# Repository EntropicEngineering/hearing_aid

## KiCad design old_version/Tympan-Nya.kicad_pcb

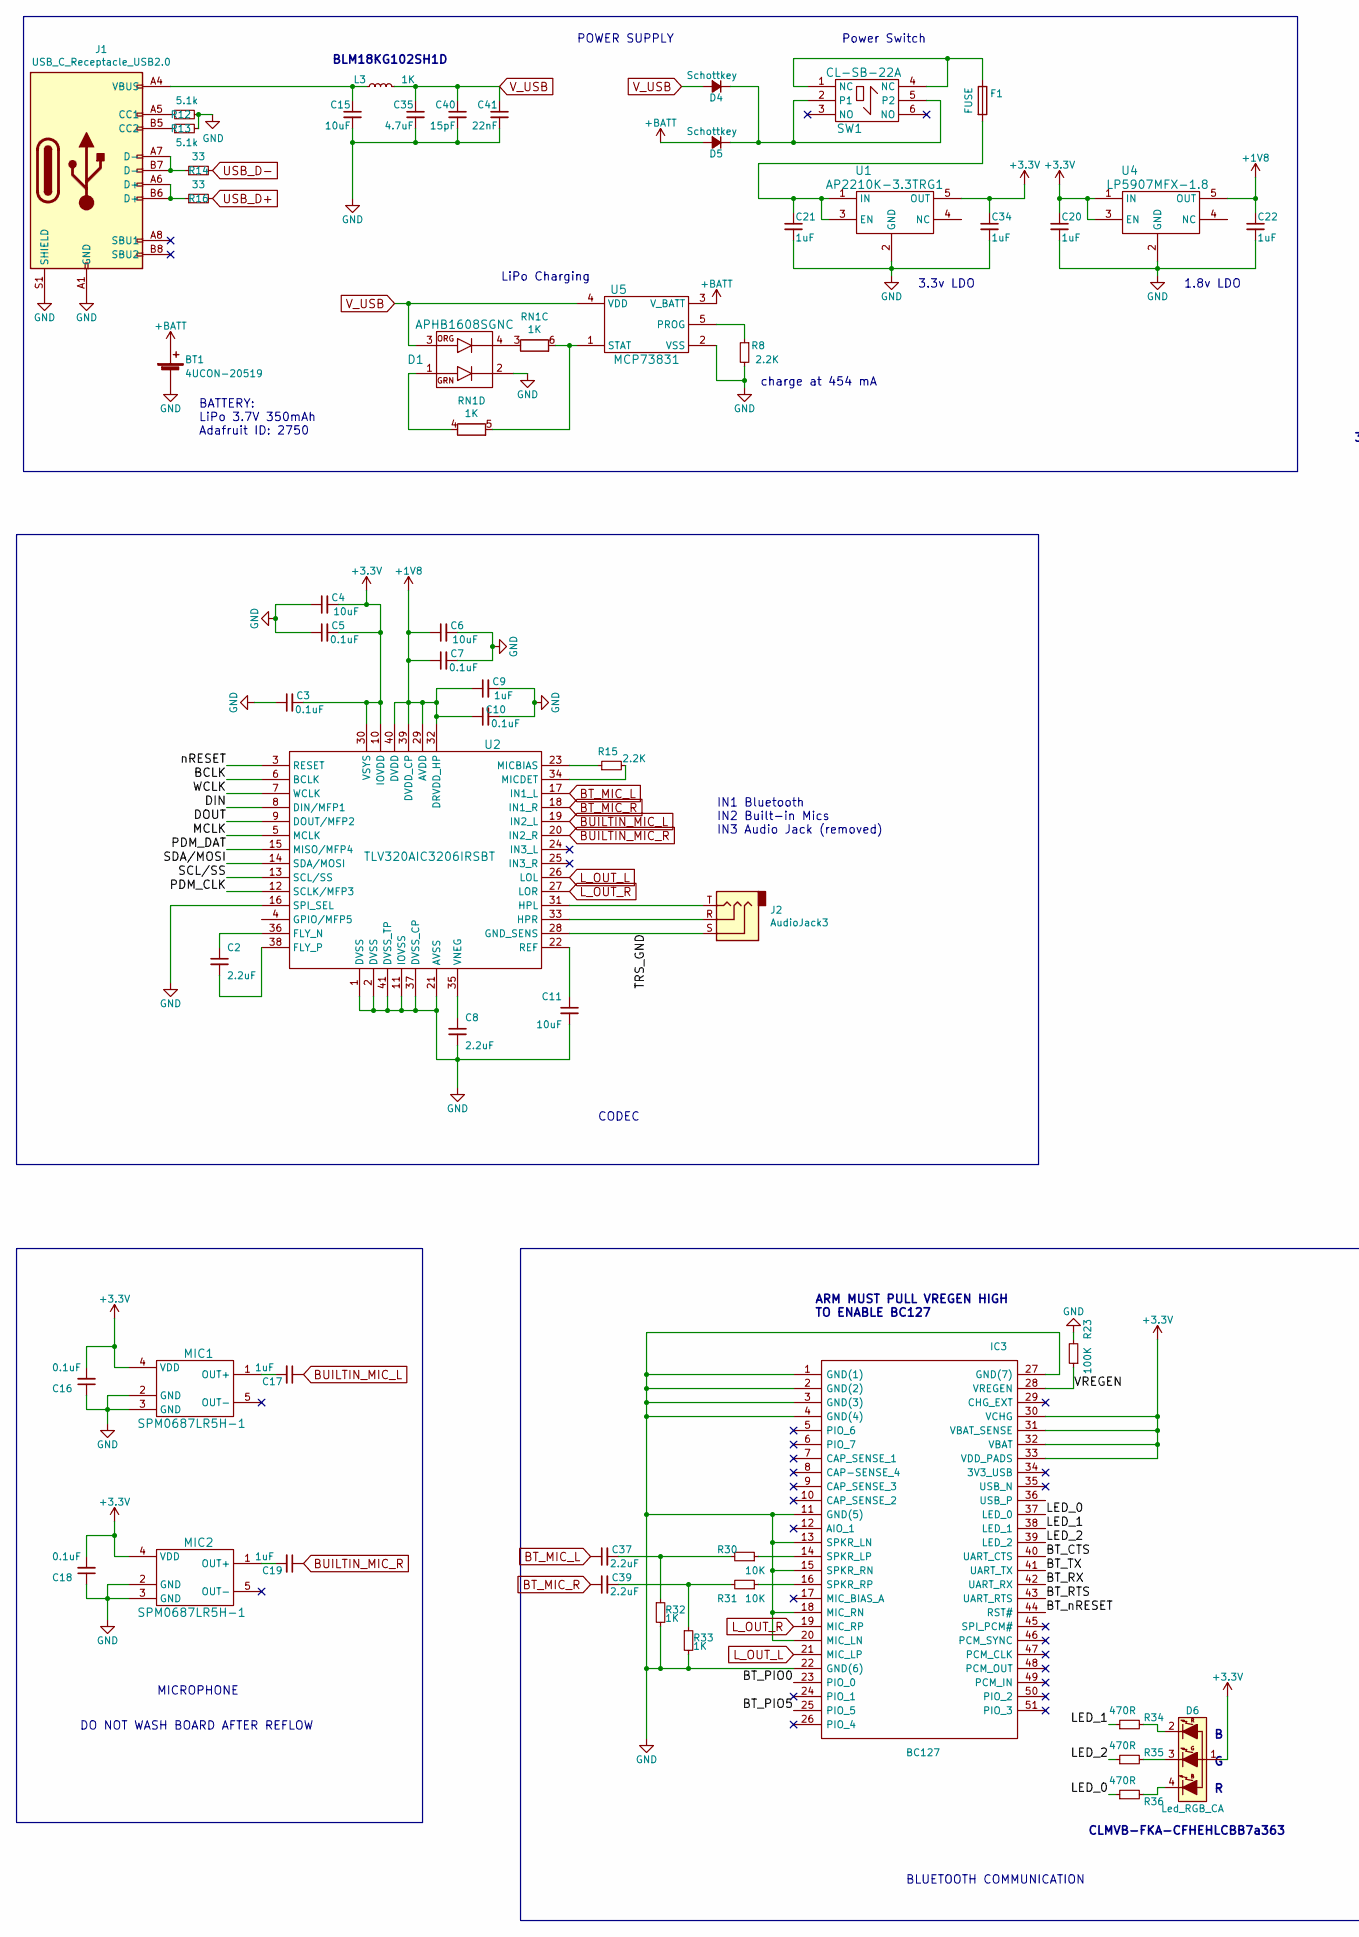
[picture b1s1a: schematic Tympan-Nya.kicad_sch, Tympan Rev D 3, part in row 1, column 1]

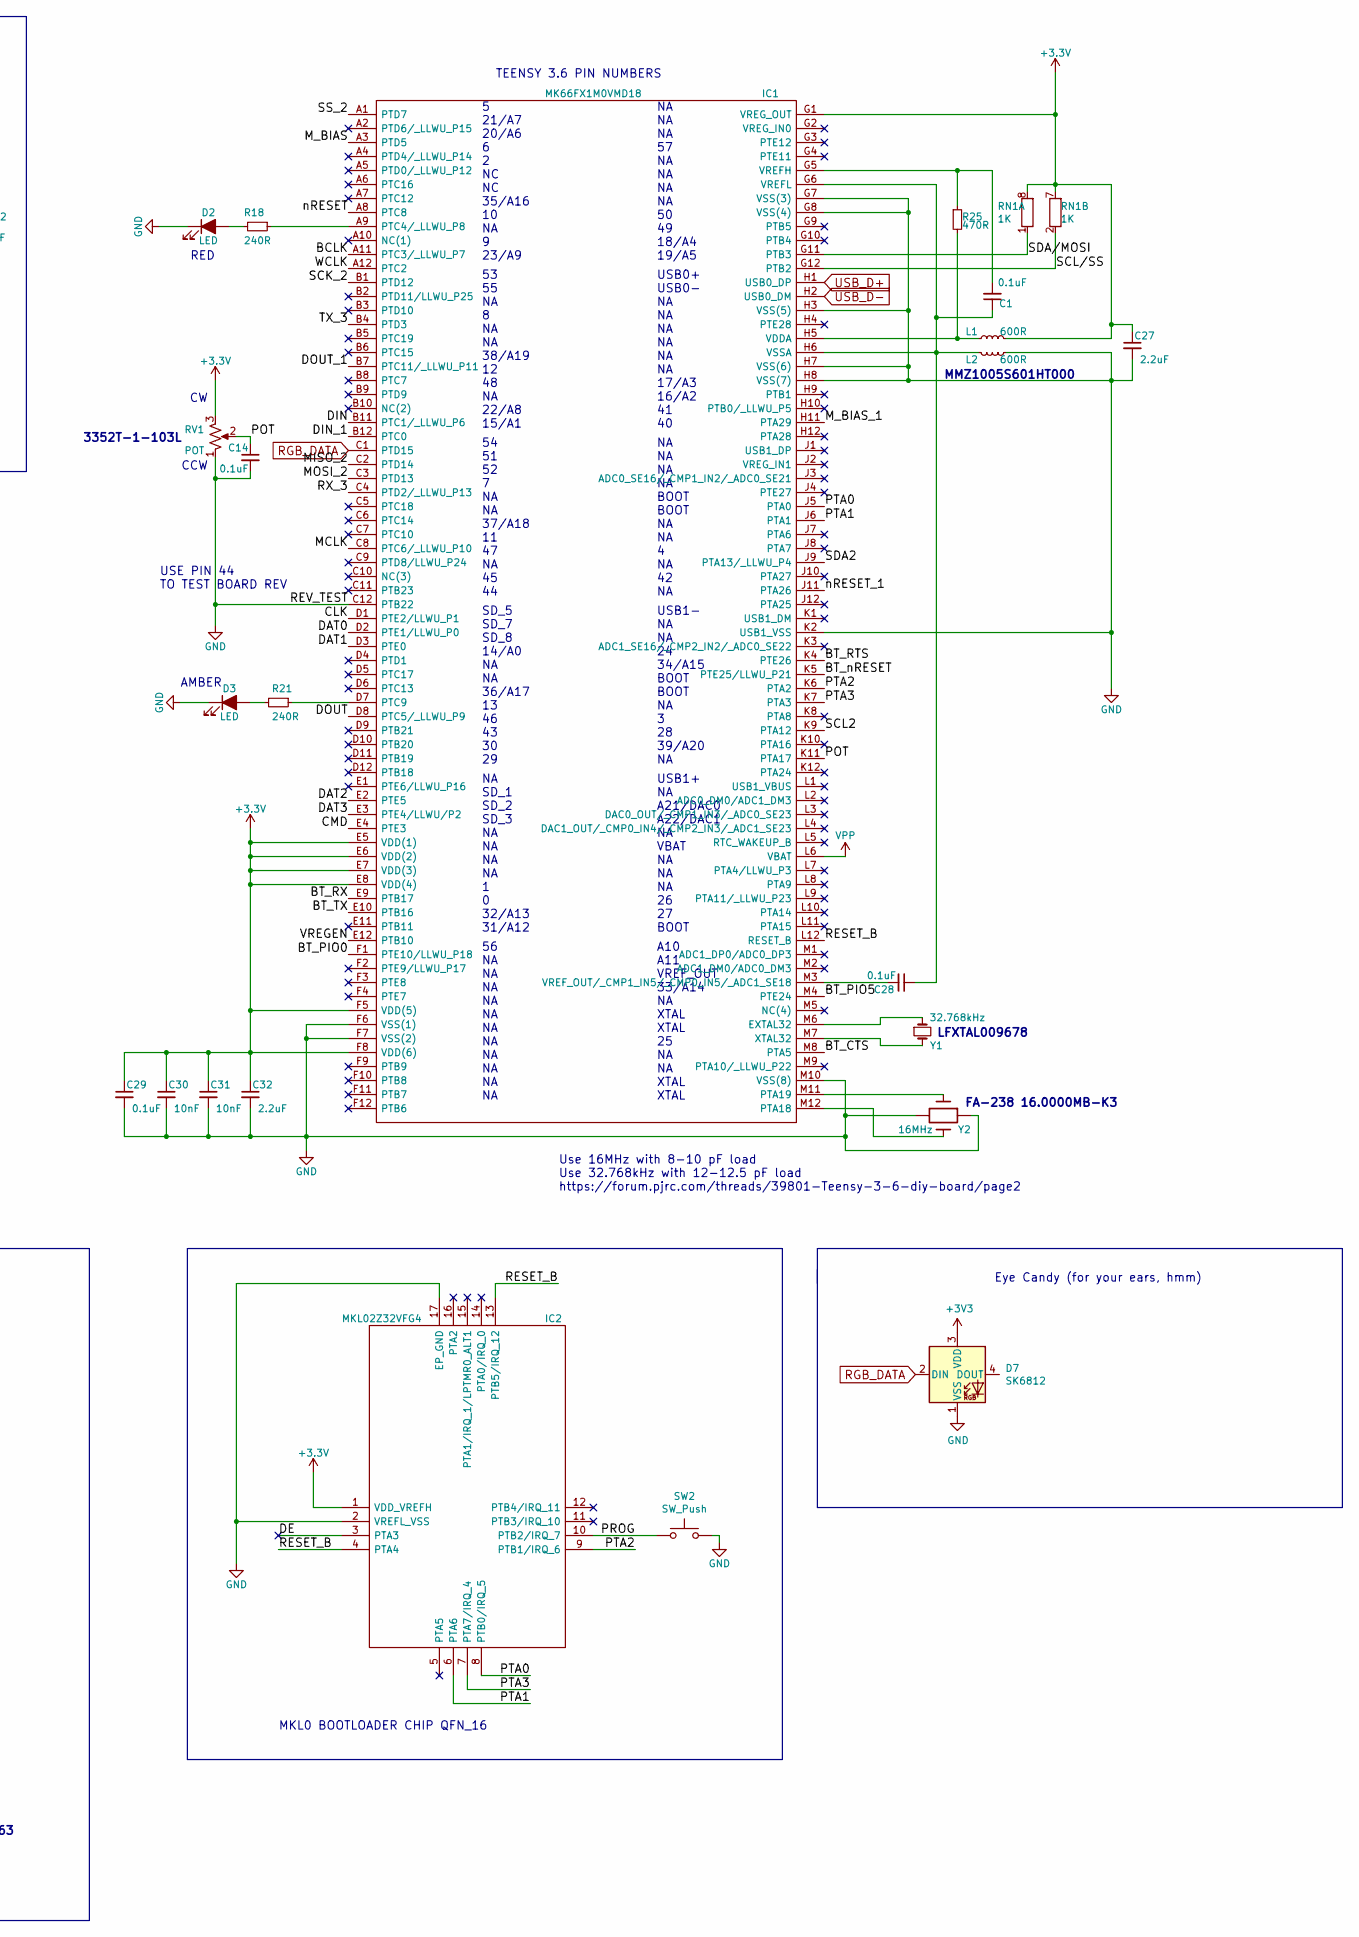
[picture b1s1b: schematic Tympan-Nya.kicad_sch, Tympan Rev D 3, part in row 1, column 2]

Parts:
BT1: 4UCON-20519; 4UCON-0217-20519
C1, C3, C5, C7, C10, C14, C16, C18, C28, C29: 0.1uF; C_0402_1005Metric
C2, C8, C27, C32, C37, C39: 2.2uF; C_0402_1005Metric
C4, C6, C11, C15: 10uF; C_0402_1005Metric
C9, C17, C19, C20, C21, C22, C34: 1uF; C_0402_1005Metric
C30, C31: 10nF; C_0402_1005Metric
C35: 4.7uF; C_0402_1005Metric
C40: 15pF; C_0402_1005Metric
C41: 22nF; C_0402_1005Metric
D1: APHB1608SGNC; ABHB1608S
D2, D3: LED; LED_0805_2012Metric
D4, D5: Schottkey; ACDBA340-HF
D6: Led_RGB_CA; CLMVB-FKA-CFHEHLCBB7a363
D7: SK6812; LED_SK6812_PLCC4_5.0x5.0mm_P3.2mm
F1: FUSE; Fuse_1206_3216Metric
IC1: MK66FX1M0VMD18; BGA-144_13.0x13.0mm_Layout12x12_P1.0mm; Manufacturer_Part_Number MK66FX1M0VMD18
IC2: MKL02Z32VFG4; QFN-16-1EP_3x3mm_P0.5mm_EP1.7x1.7mm; Manufacturer_Part_Number MKL02Z32VFG4
IC3: BC127; Manufacturer_Part_Number bc127
J1: USB_C_Receptacle_USB2.0; USB_C_Receptacle_HRO_TYPE-C-31-M-12
J2: AudioJack3; Jack_3.5mm_CUI_SJ-3523-SMT_Horizontal; DigiKey SJ-2523-SMT-TR
L1, L2: 600R; L_0402_1005Metric
L3: 1K; L_0603_1608Metric
MIC1, MIC2: SPM0687LR5H-1
R8, R15: 2.2K; R_0402_1005Metric
R12, R13: 5.1k; R_0402_1005Metric
R14, R16: 33; R_0402_1005Metric
R18, R21: 240R; R_0402_1005Metric
R23: 100K; R_0402_1005Metric
R25, R34, R35, R36: 470R; R_0402_1005Metric
R30, R31: 10K; R_0402_1005Metric
R32, R33: 1K; R_0402_1005Metric
RN1: 1K; R_Array_Convex_4x0603
RV1: POT; PinHeader_1x03_P2.54mm_Vertical
SW1: CL-SB-22A
SW2: SW_Push; SW_SPST_TL3342
U1: AP2210K-3.3TRG1; SOT-23-5
U2: TLV320AIC3206IRSBT; UQFN-40-1EP_5x5mm_P0.4mm_EP3.8x3.8mm
U4: LP5907MFX-1.8; SOT-23-5
U5: MCP73831; SOT-23-5
Y1: 32.768kHz; LFXTAL009678
Y2: 16MHz; FA_238_16.0000MB_K3

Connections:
+1V8: C6.1, C7.1, C9.1, C10.1, C22.1, U2.29 (AVDD), U2.32 (DRVDD_HP), U2.39 (DVDD_CP), U2.40 (DVDD), U4.5 (OUT)
+BATT: BT1.1 (+), D5.2 (A), U5.3 (V_BATT)
/BCLK: IC1.A11 (PTC3/_LLWU_P7), U2.6 (BCLK)
/BT_CTS: IC1.M8 (PTA5), IC3.40 (UART_CTS)
/BT_PIO0: IC1.F1 (PTE10/LLWU_P18), IC3.23 (PIO_0)
/BT_PIO5: IC1.M4 (PTE24), IC3.25 (PIO_5)
/BT_RTS: IC1.K4 (PTE26), IC3.43 (UART_RTS)
/BT_RX: IC1.E9 (PTB17), IC3.42 (UART_RX)
/BT_TX: IC1.E10 (PTB16), IC3.41 (UART_TX)
/BT_nRESET: IC1.K5 (PTE25/LLWU_P21), IC3.44 (RST#)
/CLK: IC1.D1 (PTE2/LLWU_P1)
/CMD: IC1.E4 (PTE3)
/DAT0: IC1.D2 (PTE1/LLWU_P0)
/DAT1: IC1.D3 (PTE0)
/DAT2: IC1.E2 (PTE5)
/DAT3: IC1.E3 (PTE4/LLWU/P2)
/DE: IC2.3 (PTA3)
/DIN: IC1.B11 (PTC1/_LLWU_P6), U2.8 (DIN/MFP1)
/DIN_1: IC1.B12 (PTC0)
/DOUT: IC1.D8 (PTC5/_LLWU_P9), U2.9 (DOUT/MFP2)
/DOUT_1: IC1.B7 (PTC11/_LLWU_P11)
/LED_0: IC3.37 (LED_0), R36.1
/LED_1: IC3.38 (LED_1), R34.1
/LED_2: IC3.39 (LED_2), R35.1
/MCLK: IC1.C8 (PTC6/_LLWU_P10), U2.5 (MCLK)
/MISO_2: IC1.C2 (PTD14)
/MOSI_2: IC1.C3 (PTD13)
/M_BIAS: IC1.A3 (PTD5)
/M_BIAS_1: IC1.H11 (PTA29)
/PDM_CLK: U2.12 (SCLK/MFP3)
/PDM_DAT: U2.15 (MISO/MFP4)
/POT: C14.1, IC1.K11 (PTA17), RV1.2
/PROG: IC2.10 (PTB2/IRQ_7), SW2.1
/PTA0: IC1.J5 (PTA0), IC2.8 (PTB0/IRQ_5)
/PTA1: IC1.J6 (PTA1), IC2.6 (PTA6)
/PTA2: IC1.K6 (PTA2), IC2.9 (PTB1/IRQ_6)
/PTA3: IC1.K7 (PTA3), IC2.7 (PTA7/IRQ_4)
/RESET_B: IC1.L12 (RESET_B), IC2.4 (PTA4), IC2.13 (PTB5/IRQ_12)
/RX_3: IC1.C4 (PTD2/_LLWU_P13)
/SCK_2: IC1.B1 (PTD12)
/SCL2: IC1.K9 (PTA12)
/SCL/SS: IC1.G12 (PTB2), RN1.2 (R2.1), U2.13 (SCL/SS)
/SDA2: IC1.J9 (PTA13/_LLWU_P4)
/SDA/MOSI: IC1.G11 (PTB3), RN1.1 (R1.1), U2.14 (SDA/MOSI)
/SS_2: IC1.A1 (PTD7)
/TRS_GND: J2.S, U2.28 (GND_SENS)
/TX_3: IC1.B4 (PTD3)
/VREGEN: IC1.E12 (PTB10), IC3.28 (VREGEN), R23.1
/WCLK: IC1.A12 (PTC2), U2.7 (WCLK)
/nRESET: IC1.A8 (PTC8), U2.3 (RESET)
/nRESET_1: IC1.J11 (PTA26)
BT_MIC_L: C37.1, U2.17 (IN1_L)
BT_MIC_R: C39.1, U2.18 (IN1_R)
BUILTIN_MIC_L: C17.1, U2.19 (IN2_L)
BUILTIN_MIC_R: C19.1, U2.20 (IN2_R)
GND: BT1.2 (-), C3.1, C4.1, C5.1, C6.2, C7.2, C8.2, C9.2, C10.2, C11.2, C14.2, C15.2, C16.1, C18.1, C20.2, C21.2, C22.2, C27.2, C29.2, C30.2, C31.2, C32.2, C34.2, C35.2, C40.2, C41.2, D1.2, D2.1 (K), D3.1 (K), D7.1 (VSS), IC1.C12 (PTB22), IC1.F6 (VSS(1)), IC1.F7 (VSS(2)), IC1.G7 (VSS(3)), IC1.G8 (VSS(4)), IC1.H3 (VSS(5)), IC1.H7 (VSS(6)), IC1.H8 (VSS(7)), IC1.K2 (USB1_VSS), IC1.M10 (VSS(8)), IC2.2 (VREFL_VSS), IC2.17 (EP_GND), IC3.1 (GND(1)), IC3.2 (GND(2)), IC3.3 (GND(3)), IC3.4 (GND(4)), IC3.11 (GND(5)), IC3.13 (SPKR_LN), IC3.15 (SPKR_RN), IC3.18 (MIC_RN), IC3.20 (MIC_LN), IC3.22 (GND(6)), IC3.27 (GND(7)), J1.A1 (GND), J1.A12 (GND), J1.B1 (GND), J1.B12 (GND), J1.S1 (SHIELD), L2.2, MIC1.2 (GND), MIC1.3 (GND), MIC2.2 (GND), MIC2.3 (GND), R8.2, R12.2, R13.2, R23.2, R32.2, R33.2, RV1.1, SW2.2, U1.2 (GND), U2.1 (DVSS), U2.2 (DVSS), U2.11 (IOVSS), U2.16 (SPI_SEL), U2.21 (AVSS), U2.37 (DVSS_CP), U2.41 (DVSS_TP), U4.2 (GND), U5.2 (VSS), Y2.2, Y2.4
L_OUT_L: IC3.21 (MIC_LP), U2.26 (LOL)
L_OUT_R: IC3.19 (MIC_RP), U2.27 (LOR)
unnamed: C1.1, C28.1, IC1.G6 (VREFL), IC1.H6 (VSSA), L2.1
unnamed: C1.2, IC1.G5 (VREFH), R25.1
unnamed: C2.1, U2.36 (FLY_N)
unnamed: C2.2, U2.38 (FLY_P)
unnamed: C8.1, U2.35 (VNEG)
unnamed: C11.1, U2.22 (REF)
unnamed: C15.1, J1.A4 (VBUS), J1.A9 (VBUS), J1.B4 (VBUS), J1.B9 (VBUS), L3.1
unnamed: C17.2, MIC1.1 (OUT+)
unnamed: C19.2, MIC2.1 (OUT+)
unnamed: C21.1, F1.2, U1.1 (IN), U1.3 (EN)
unnamed: C28.2, IC1.M3 (VREF_OUT/_CMP1_IN5/_CMP0_IN5/_ADC1_SE18)
unnamed: C37.2, R30.2, R32.1
unnamed: C39.2, R31.2, R33.1
unnamed: D1.1, RN1.4 (R4.1)
unnamed: D1.4, RN1.3 (R3.1)
unnamed: D2.2 (A), R18.2
unnamed: D3.2 (A), R21.2
unnamed: D4.1 (K), D5.1 (K), SW1.2 (P1), SW1.5 (P2)
unnamed: D6.2 (R), R34.2
unnamed: D6.3 (G), R35.2
unnamed: D6.4 (B), R36.2
unnamed: F1.1, SW1.1 (NC), SW1.4 (NC)
unnamed: IC1.A9 (PTC4/_LLWU_P8), R18.1
unnamed: IC1.D7 (PTC9), R21.1
unnamed: IC1.H5 (VDDA), L1.1, R25.2
unnamed: IC1.M6 (EXTAL32), Y1.1
unnamed: IC1.M7 (XTAL32), Y1.2
unnamed: IC1.M11 (PTA19), Y2.1
unnamed: IC1.M12 (PTA18), Y2.3
unnamed: IC3.14 (SPKR_LP), R30.1
unnamed: IC3.16 (SPKR_RP), R31.1
unnamed: J1.A5 (CC1), R12.1
unnamed: J1.A6 (D+), J1.B6 (D+), R16.1
unnamed: J1.A7 (D-), J1.B7 (D-), R14.1
unnamed: J1.B5 (CC2), R13.1
unnamed: J2.R, U2.33 (HPR)
unnamed: J2.T, U2.31 (HPL)
unnamed: R8.1, U5.5 (PROG)
unnamed: R15.1, U2.23 (MICBIAS)
unnamed: R15.2, U2.34 (MICDET)
unnamed: RN1.5 (R4.2), RN1.6 (R3.2), U5.1 (STAT)
RGB_DATA: D7.2 (DIN), IC1.C1 (PTD15)
USB_D+: IC1.H1 (USB0_DP), R16.2
USB_D-: IC1.H2 (USB0_DM), R14.2
VPP: IC1.L6 (VBAT)
V_USB: C35.1, C40.1, C41.1, D1.3, D4.2 (A), L3.2, U5.4 (VDD)

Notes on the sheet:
DO NOT WASH BOARD AFTER REFLOW
MICROPHONE
BATTERY: LiPo 3.7V 350mAh Adafruit ID: 2750
BLM18KG102SH1D
POWER SUPPLY
LiPo Charging
CODEC
IN1 Bluetooth IN2 Built-in Mics IN3 Audio Jack (removed)
ARM MUST PULL VREGEN HIGH TO ENABLE BC127
charge at 454 mA
BLUETOOTH COMMUNICATION
Power Switch
3.3v LDO
CLMVB-FKA-CFHEHLCBB7a363
B G R
1.8v LDO
3352T-1-103L
USE PIN 44 TO TEST BOARD REV
CW CCW
RED
AMBER
MKL0 BOOTLOADER CHIP QFN_16
5 21/A7 20/A6 6 2 NC NC 35/A16 10 NA 9 23/A9
53 55 NA 8 NA NA 38/A19 12 48 NA 22/A8 15/A1
54 51 52 7 NA NA 37/A18 11 47 NA 45 44
SD_5 SD_7 SD_8 14/A0 NA NA 36/A17 13 46 43 30 29
NA SD_1 SD_2 SD_3 NA NA NA NA 1 0 32/A13 31/A12
56 NA NA NA NA NA NA NA NA NA NA NA
TEENSY 3.6 PIN NUMBERS
Use 16MHz with 8-10 pF load Use 32.768kHz with 12-12.5 pF load https://forum.pjrc.com/threads/39801-Teensy-3-6-diy-board/page2
NA NA NA 57 NA NA NA NA 50 49 18/A4 19/A5
USB0+ USB0- NA NA NA NA NA NA 17/A3 16/A2 41 40
NA NA NA NA BOOT BOOT NA NA 4 NA 42 NA
USB1- NA NA 24 34/A15 BOOT BOOT NA 3 28 39/A20 NA
USB1+ NA A21/DAC0 A22/DAC1 NA VBAT NA NA NA 26 27 BOOT
A10 A11 VREF_OUT 33/A14 NA XTAL XTAL 25 NA NA XTAL XTAL
LFXTAL009678
MMZ1005S601HT000
FA-238 16.0000MB-K3
Eye Candy (for your ears, hmm)

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
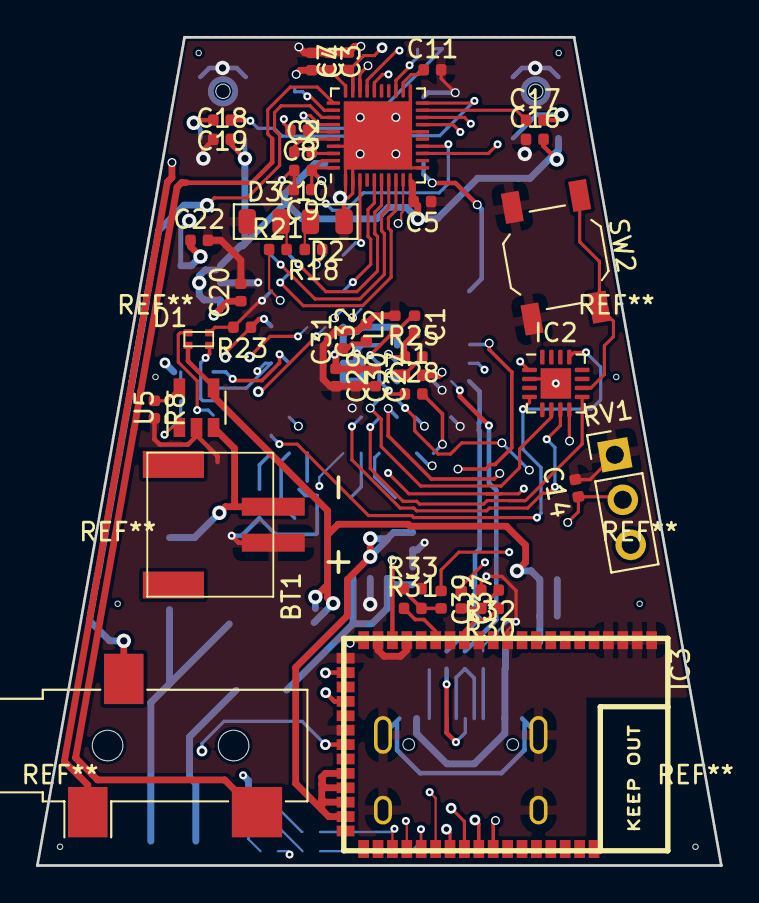
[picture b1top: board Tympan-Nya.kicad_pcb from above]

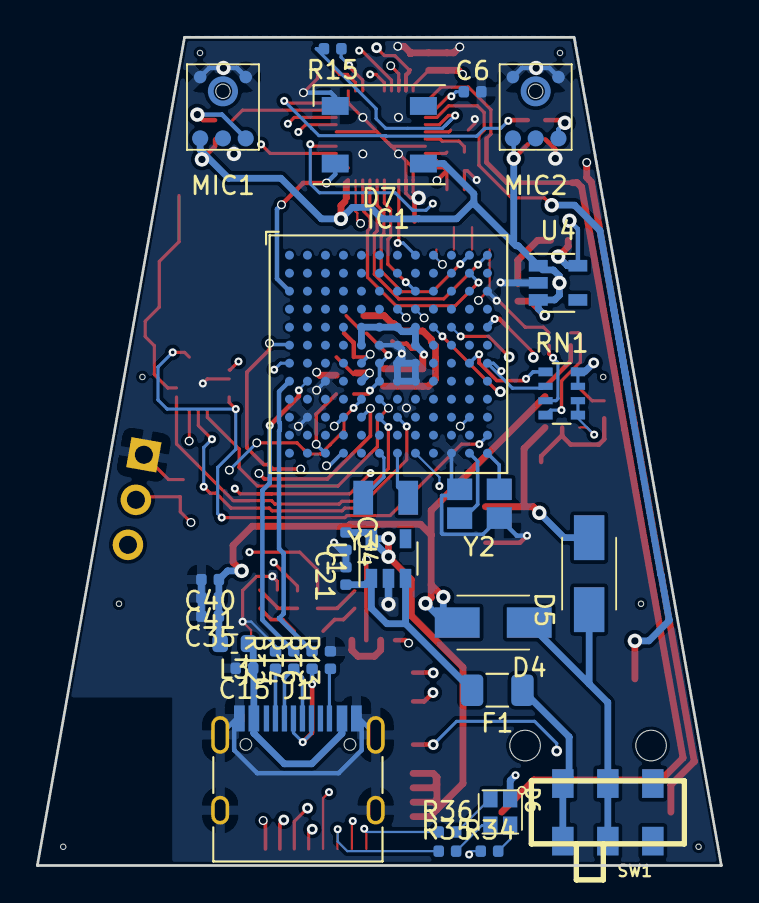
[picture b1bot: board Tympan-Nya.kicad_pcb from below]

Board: 4 copper layers, 38.0 x 46.0 mm, 78 parts (31 on the bottom side), 82 nets.

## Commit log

2021-06-19 Initial commit.
2021-08-15 Added many files.
2021-08-15 Added block diagram.
2021-08-15 notes
2021-08-16 add .gitignore for History and __Previews
2021-08-16 Simplify USB Type-C
2021-08-16 LiPo charging schematic
2021-08-16 revert USB-C connector, use consistent symbols
